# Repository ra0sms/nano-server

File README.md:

# Nano Server — Remote Radio Station Server

**Nano Server** is a server-side component of a remote ham radio station system. It runs on a **NanoPi NEO** single-board computer with **Armbian** and provides audio streaming, PTT control via GPIO, video streaming, relay switching, CAT interface forwarding, CW keying, and a web-based configuration interface.

Desktop client software: https://github.com/ra0sms/caesar-client-desktop

---

## Features

- 🎙️ **Bidirectional audio** over UDP (GStreamer + Opus codec)
- 📡 **PTT control** via GPIO with client reachability monitoring
- 📷 **Video streaming** via mjpg-streamer (MJPEG over HTTP)
- 🔌 **Relay control** via I2C (2×PCF8574T, 16 relays total)
- 🌐 **Web interface** — relays, TRX, band relay rules, audio, config, settings, self-update (single UI on port 5050)
- 🔗 **CAT interface** forwarding over TCP (Icom CI-V, Kenwood and Elecraft protocols; Elecraft is the Kenwood protocol with RTS/DTR held low, as the K3 needs)
- 🔄 **UART1 transparent relay** — CAT data duplicated to physical UART1 port for local computer access
- 🔒 **Fail-safe** — PTT is forced OFF when client disconnects; a CW message in progress is stopped and the CW key line released too (with break-in the radio would otherwise keep transmitting on the key alone)
- 🚫 **PTT Lock** — relay switching (manual and band relay) is blocked while PTT is active to prevent accidental antenna switching during transmission
- 🎛️ **Band Relay Rules** — automatic relay switching based on transceiver frequency
- 🔑 **CW Keyer** — Winkeyer protocol over UDP, generates Morse code on GPIO PC1
- 🔄 **Self-update** — checks GitHub for a newer release tag, shows its changelog, and applies it (`git pull` + restart of all related systemd services) from the web UI

---

## Hardware

| Component | Details |
|---|---|
| SBC | NanoPi NEO (Allwinner H3) |
| OS | Armbian (Debian Bookworm or later) |
| Audio | USB sound card (C-Media USB Audio Device) |
| Camera | USB webcam on `/dev/video1` |
| Relay board | 2× I2C GPIO expander at `0x20` / `0x21` |
| CAT interface | USB-to-Serial (port chosen in web Settings tab, e.g. `/dev/ttyUSB0`) |
| CAT UART1 relay | Physical UART1 on `/dev/ttyS1` (pins 8-TX, 10-RX) |
| CON LED | GPIO PC2 (line 66) |
| PTT output | GPIO PC3 (line 67) |
| CW Keyer output | GPIO PC1 (line 65) |

---

## Architecture

```
Client PC                          NanoPi NEO (Server)
─────────────────────────────────────────────────────────
                    UDP :5000  ←──  Audio TX (mic → client)
                    UDP :5000  ──→  Audio RX (client → speaker)
                    UDP :5001  ──→  PTT commands (0/1)
                    UDP :5002  ←→   Ping / RTT monitoring
                    UDP :5003  ──→  CW Keyer (Winkeyer protocol, UDP)
                    TCP :5050  ←──  Web UI (Flask): relays, TRX, band relay, audio, config, settings, update (live status over SSE)
                    TCP :6789  ←──  CW XML-RPC (PyWinKeyerSerial / not1mm)
                    TCP :3001  ←──  CAT (Icom CI-V or Kenwood)

Local PC (UART1)                   NanoPi NEO (Server)
─────────────────────────────────────────────────────────
                    UART1 (ttyS1) ←→  Transparent CAT relay (bidirectional)
```

### Systemd services

| Service | Description |
|---|---|
| `ptt_server` | PTT + CW Keyer + client monitor + ping responder (single service, all GPIO) |
| `audio_server` | GStreamer audio TX (server mic → client) |
| `audio_client_on_server` | GStreamer audio RX (client → server speaker) |
| `relay-web` | Web UI: relays, TRX, band relay, audio, config, settings, update (port 5050) |
| `mjpeg-streamer` | MJPEG video stream from USB camera (localhost:8081 only; viewed through the web panel login) |
| `alsa_restore` | Restores ALSA mixer state at boot |

---

## Installation

### 1. Flash Armbian to SD card and boot NanoPi NEO

### 2. Clone the repository

```bash
git clone https://github.com/ra0sms/nano-server.git
cd /home/pi/nano-server
```

### 3. Run the install script as root

```bash
sudo bash install_server.sh
```

The script will:
- Install all required packages (GStreamer, Flask, gpiod, mjpg-streamer, etc.)
- Build and install **mjpg-streamer** from source
- Create `client_ip.cfg`, `server_ip.cfg`, and `web/password.txt` with defaults
- Configure hardware overlays in `/boot/armbianEnv.txt`
- Register and start all systemd services
- Add sudoers entries for `restart_services_on_server.sh`, `systemctl restart/stop/start relay-web`, and `alsactl store` (so Audio tab volume changes persist across reboot)

### 4. Set IP addresses

```bash
echo '192.168.1.100' > /home/pi/nano-server/client_ip.cfg   # IP of the client PC
echo '192.168.1.10'  > /home/pi/nano-server/server_ip.cfg   # IP of this server
```

Or use the web interface at `http://<server-ip>:5050/`.

### 5. Change the default password for the web panel

```bash
echo 'yourpassword' > /home/pi/nano-server/web/password.txt
```

### 6. (Optional) Fix ALSA card order

If you have multiple USB audio devices (e.g., webcam with mic), the C-Media USB Audio card may not be card 0. Run:

```bash
sudo bash /home/pi/nano-server/fix_alsa_card_order.sh
sudo reboot
```

### 7. Reboot

```bash
sudo reboot
```

---

## Armbian Hardware Configuration

The script `setup_armbian_env.sh` patches `/boot/armbianEnv.txt` to enable the required device tree overlays. It **never modifies** `rootdev` or `rootfstype` so the system remains bootable.

To apply manually on a running system:

```bash
sudo bash /home/pi/nano-server/setup_armbian_env.sh
sudo reboot
```

Required overlays: `i2c0 uart1 uart2 uart3 usbhost0 usbhost1 usbhost2 usbhost3 w1-gpio`

---

## Web Interface — port 5050

Access at `http://<ip>:5050/` (password protected).
Default password: `1234` — change it in `web/password.txt`.

| Tab | Description |
|---|---|
| Main | Relay switching (16 relays, toggle/switch modes) and camera view |
| TRX | Transceiver frequency, band, mode display, and **Band Relay** frequency-based automatic relay switching rules |
| Audio | Speaker and mic level control via ALSA, audio stream settings (sample rate/buffer), restart audio services |
| Config | IP addresses, saved profiles, network status (client RTT / connection status, local IP) |
| Settings | Relay names, group modes, TRX serial port and protocol, UART1 transparent relay toggle |
| Update | Check GitHub for a newer release, view its changelog, apply the update and restart the web panel |

### Persistent Status Bar & Real-Time Updates

A **status bar** is shown at the top of every tab with the current PTT state, the transceiver online/frequency indicator, and the client link latency (RTT):

- **PTT** — turns red (`● PTT: ON`) while transmitting, grey otherwise.
- **TRX** — `🟢 ONLINE` / `🔴 OFFLINE` plus the live frequency.
- **Client** — round-trip time to the client PC in milliseconds.

Live values are pushed to the browser over **Server-Sent Events** (SSE, `GET /events`). The server sends a combined snapshot (PTT, relay state, TRX frequency/band/mode, client RTT, band-relay current state) that is emitted only when it changes, replacing the previous per-tab HTTP polling every 2 s. This makes status changes appear immediately and reduces load on the device. The SSE stream requires an authenticated session (cookies are sent automatically by the browser) and reconnects automatically if dropped.

### Band Relay Rules

Configure which relays activate for each frequency range (in kHz). Rules use `from ≤ freq < to` logic (lower bound inclusive, upper bound exclusive). To avoid gaps, set `to` of one rule equal to `from` of the next.

Example:
- `1800-1840` kHz → relays 1, 2
- `1840-1900` kHz → relays 3, 4
- `7000-7300` kHz → relays 5, 6

Auto-switching can be toggled on/off via a checkbox in the TRX tab. Rules are validated on the server (numeric `from < to` in kHz, relay numbers 1–16); if `web/band_rules.json` is unreadable at startup, it is renamed to `band_rules.json.invalid` and the default rules are used.

**Group-scoped auto-switching:** auto-switching only touches the relay group(s) that the configured rules actually reference, leaving the other group fully manual:

- If the saved rules only use relays **1–8**, then relays **9–16** are never reset or switched automatically — they can be selected manually and their state is preserved across every frequency change (and vice versa).
- If the rules reference relays from both groups, both are auto-managed (all selected relays are reset and re-applied as before).
- If no rule references any relay, auto-switching leaves all 16 relays untouched.

This makes it possible to dedicate one relay group to automatic antenna/band switching while keeping the other group for manually-controlled devices.

**Switching only on a band change, with confirmation:** relays are switched only when the frequency moves into a range with a *different* relay set, and only after two frequency readings at least 0.3 s apart agree. This means:

- a single corrupted CAT frame can't flip the antenna;
- tuning back and forth across a range boundary doesn't chatter the relays;
- a relay toggled by hand inside an auto-managed group stays as set until the next band change (it is no longer reset on every CAT reading).

While a band change waits for its confirming reading, the server polls the transceiver right away (subject to the external-program collision guard), so the switch still happens promptly. Saving the rules or re-enabling auto-switching re-applies them on the next reading.

### PTT Lock — Relay Protection During Transmission

When PTT is active (transmitting), all relay switching is automatically blocked to prevent accidental antenna switching during transmission. This protects both the transceiver and the antenna system.

**How it works:**
1. [`combined_ptt_service.py`](network/combined_ptt_service.py) broadcasts the GPIO PTT status via UDP on `127.0.0.1:5004` on every change **and as a heartbeat every ~0.3 s**
2. [`web/app.py`](web/app.py) listens for these broadcasts in a background thread. If no status has arrived for 1.5 s (the web panel just restarted, or `ptt_server` is stopped/crashed), the PTT state is treated as **unknown and relays stay locked**
3. **CAT PTT** is tracked too, since programs like JTDX/WSJT-X/flrig often key the radio over CAT instead of the GPIO line:
   - TX/RX commands external programs send through the TCP port or UART1 relay (Kenwood `TX…;` / `RX…;`, Icom CI-V `1C 00 01` / `1C 00 00`)
   - the radio's own reports: TX/RX flag in the Kenwood `IF` reply and `TX…;`/`RX…;` auto-information, the Icom reply to `1C 00` (the server polls it on alternate poll cycles)
   - if the transceiver stops answering CAT for 5 s, the CAT TX state is cleared
4. Both manual relay toggle and automatic band relay switching are blocked while GPIO PTT is on, CAT PTT is on, or the PTT state is unknown
5. The web interface visually disables relay buttons (dimmed, `not-allowed` cursor). The status bar shows `PTT: ON`, `PTT: ON (CAT)`, or an orange `PTT: NO STATUS` when `ptt_server` isn't reporting

**Blocked operations:**
- Manual relay toggle via web UI buttons
- Automatic band relay switching when transceiver frequency changes
- Direct API calls to `POST /toggle/<n>` (server-side check)
- **Retuning from the web UI** — frequency step, band buttons and `/trx/set_freq`: band relays can't follow during TX, so a band change would leave the transmitter keyed into the previous band's antenna (the request is refused with HTTP 409 and a message in the UI). Frequency steps are also refused while the transceiver is offline, instead of stepping from a made-up frequency

---

### UART1 Transparent CAT Relay

The server can transparently relay all CAT data between the transceiver (connected via the USB-to-Serial CAT port selected in web Settings) and a local computer connected to the **UART1** physical port (`/dev/ttyS1`, pins 8-TX, 10-RX on NanoPi NEO). This allows two clients to share the same CAT connection simultaneously:

- **Remote client** — connects via TCP port 3001 over the network. Only `127.0.0.1`, the client IP from `client_ip.cfg`, and the IPs listed in `tcp_allowed_ips` in `web/trx_config.json` (edit the file, then restart `relay-web`; e.g. `"tcp_allowed_ips": ["192.168.1.50"]`) may connect; other connections are closed immediately, since this port can key and retune the transmitter
- **Local computer** — connected directly via UART1 (e.g., a PC next to the server)

**How it works:**

1. All data received from the transceiver on the CAT port is duplicated to both TCP clients and UART1
2. All data received from UART1 is written back to the CAT port (and thus forwarded to the transceiver)
3. All data received from TCP clients is written to the CAT port (existing behavior)

**Configuration** (in [`web/trx_config.json`](web/trx_config.json) or via web UI Settings tab):

```json
{
    "uart1_enabled": true,
    "uart1_port": "/dev/ttyS1"
}
```

The UART1 baudrate is automatically set to match the CAT port baudrate.

**Replies to the server's own requests are not forwarded.** The server's own polls (and the web UI's TRX commands) would otherwise produce replies that external programs take as answers to their own requests, causing "unexpected reply" errors and retries in Hamlib/JTDX/flrig:

- **Icom CI-V:** the server talks to the radio from its own controller address, **Server CI-V Address** in Settings (`server_addr`, default `0xE1`), not the `0xE0` that flrig/JTDX/Hamlib use (`ctrl_addr`). The radio replies to the sender's address, so frames to or from `server_addr` (including the echo on a single-wire CI-V bus) are decoded for the web UI but not passed to TCP clients or UART1. If some radio only works with `0xE0`, set Server CI-V Address to `0xE0`: everything is then forwarded, as in older versions.
- **Kenwood:** there are no addresses, so after each `IF;` poll the next `IF…;` reply (within 0.5 s) is kept back from external programs. If UART1 is unavailable (e.g., overlay not enabled), the server logs a warning and continues without it.

**Web UI toggle:** The **Settings → Transceiver Settings** tab now includes a **"UART1 transparent relay"** checkbox. It can be turned on/off directly from the web interface and takes effect immediately (the relay is re-initialized without restarting the service).

**Poller behavior with the relay enabled:**

When the UART1 transparent relay is enabled, the CAT bus can be owned by an external program on the PC (e.g. **flrig**, **TR4W**, **Hamlib**). While the external program is **actively** exchanging data, the server's internal poller backs off so its queries do not interleave with the PC's requests on the same line and corrupt the response stream.

However, the server now **automatically resumes its own polling whenever the external program is silent or absent**:

- **Relay ON + external program active** → the server's poller stays quiet; the PC program reads the transceiver directly, and the web **TRX tab** stays updated passively by decoding the responses that flow through the bridge.
- **Relay ON + external program silent/absent** → the server only skips its own poll while an external controller (via UART1 or a TCP client) has sent something within the last 0.3 s, or while the radio has answered within the last 2 s (someone is already keeping the frequency fresh). Otherwise it polls the transceiver itself, so the web **TRX tab** still shows the live frequency/mode even when no PC program is running. As soon as the external program sends traffic again, the poller hands the port back within one poll cycle.
- **Relay OFF** → internal poller enabled; the web interface queries the transceiver itself and updates the TRX tab even when no PC program is connected.

This behavior applies to **both** CAT protocols (Icom CI-V and Kenwood).

"Recently" means the radio has reported the **active** frequency in the last 2 s; other CAT traffic doesn't count (e.g. Hamlib reading only the inactive VFO).

**What the web panel decodes:**

- **Icom CI-V:** frequency and mode replies (`03`/`04`) and the radio's own **transceive** reports (`00`/`01`). With *CI-V Transceive* enabled in the radio's menu, frequency changes arrive as soon as the dial moves, so band relays react without waiting for a poll. Modes: LSB, USB, AM, CW, CW-R, RTTY, RTTY-R, FM, WFM, DV, DD. 6-byte frequencies (10 GHz+ bands, IC-905) are supported.
- **Kenwood:** `IF` (frequency, mode, TX/RX and **active VFO**), `FA`/`FB`, `MD`, `FR`. `FA`/`FB` only update the displayed frequency and band relays when they are for the VFO the radio is operating on (learned from `IF`, `FR` reports and `FR` commands external programs send). Otherwise, working on VFO B would switch antennas by VFO A's frequency. Frequency changes from the web UI are sent to the active VFO (`FB` when on VFO B).

**Stability & auto-recovery:**

All writes to the CAT port are serialized through a single thread lock (`ser_lock`), and data from each external source (every TCP client and UART1) is first split into **whole CAT frames** (terminated by `;` for Kenwood, `0xFD` for CI-V) — only complete frames are written. So a command that arrives in pieces (e.g. `F` in one TCP segment and `A;` in the next) can never have the poller's or another client's frame inserted into its middle. An unterminated tail is passed through as-is after 0.5 s. The CAT port and UART1 are read without a fixed 100 ms wait, so replies reach JTDX/flrig and UART1 immediately. Additionally, if the CAT serial port raises a read error (e.g. a temporary USB hiccup or the transceiver is powered off), the server now **automatically closes and reopens the serial ports** with retries instead of silently stalling — so a remote `JTDX`, `flrig`, or `WSJT-X` session no longer needs a full service restart to recover. Manually re-initializing from the web UI (Reconnect button / `POST /trx/reinit`) and re-initializing after a config change are also guarded by the same lock.

**Prerequisite:** UART1 overlay must be enabled in `/boot/armbianEnv.txt`:
```
overlays=i2c0 uart1 uart2 uart3 usbhost0 usbhost1 usbhost2 usbhost3 w1-gpio
```

---

## Profiles

Up to 5 configuration profiles (server IP, client IP, audio settings) can be saved and loaded from the web configuration interface. Profile files are stored in `profiles/`.

---

## Restarting Services

To restart all runtime services at once:

```bash
sudo /home/pi/nano-server/restart_services_on_server.sh
```

Or restart individual services:

```bash
sudo systemctl restart ptt_server.service
sudo systemctl restart audio_server.service
```

To restart the web panel from the UI, use the **"Restart Web Panel"** button on the Update tab (requires sudoers NOPASSWD for `systemctl restart relay-web`). The **"Restart Audio Services"** button on the Audio tab restarts `audio_server`, `audio_client_on_server`, `mjpeg-streamer`, and `ptt_server` (via `restart_services_on_server.sh`).

To reload `client_ip.cfg` without restarting the PTT service:

```bash
sudo systemctl kill -s SIGHUP ptt_server.service
```

---

## Software Update

The **Update** tab checks GitHub for a newer release and applies it without needing SSH access to the server.

- **Check for Update** fetches tags from `origin` and compares the highest `vX.Y.Z` tag to the version reachable from the currently checked-out commit (`git describe --tags`). If a newer one exists, it shows every `CHANGELOG.txt` section newer than the current version (not just the latest one), read directly from the fetched tag so it's visible even before pulling.
- **Update** runs `git pull --ff-only`, then restarts `audio_server`, `audio_client_on_server`, `mjpeg-streamer`, and `ptt_server` (via `restart_services_on_server.sh`), and finally restarts `relay-web` itself.
- Before pulling, it refuses if the checkout has local changes to any **tracked** file, or **any untracked file at all**, outside of the app's own runtime-state files (`web/config.json`, `audio/audio_config.cfg`, `web/trx_config.json`, `web/band_rules.json` — these are gitignored and rewritten by the app itself, so their local content is preserved across the pull automatically). A stray file left in the checkout (e.g. a manual backup) will block the update until it's removed or committed elsewhere.

Cutting a new release: add a `## vX.Y.Z (date)` section with a bullet list to the top of `CHANGELOG.txt`, commit, then tag and push:

```bash
git tag vX.Y.Z
git push origin main
git push origin vX.Y.Z
```

---

## Audio Configuration

Edit `audio/audio_config.cfg`:

```ini
RATE=48000       # sample rate: 48000 or 24000 Hz
LATENCY=100000   # buffer time in microseconds (100 ms)
```

Or use the **Audio Stream Settings** section on the **Audio** page in the web UI.

The web panel auto-detects the ALSA card (looks for C-Media USB Audio in `/proc/asound/cards`) and the speaker control name. Mic capture is hardcoded to `numid=8` (`Mic Capture Volume`).

---

## CW Keyer (Winkeyer Protocol)

The CW Keyer is integrated into the **`ptt_server`** service (single process, single GPIO request). It implements the **K1EL Winkeyer protocol** over UDP, generating Morse code (CW) on **GPIO PC1** (line 65).

All GPIO lines (CW=PC1, CON=PC2, PTT=PC3) are requested in a single `gpiod.request_lines()` call to avoid conflicts between separate processes on the same gpiochip.

### How it works

1. The client sends Winkeyer protocol commands via UDP to port **5003**
2. The server buffers ASCII characters and sends them as CW on GPIO PC1
3. The output pin (PC1) drives a transistor/keying circuit connected to the transceiver

### Supported commands

| Byte | Command | Description |
|---|---|---|
| `0x00` + WPM | Set speed | WPM value (5-99) |
| `0x02` | Start sending | Begin transmitting buffer |
| `0x03` | Clear buffer | Reset and stop |
| `0x0A` (LF) | Start sending | Same as 0x02 |
| `0x1B` | Immediate stop | Abort transmission |
| `0x1F` | Request status | Reply: 0x00 (idle) or 0x01 (busy) |
| `0x20`-`0x7E` | ASCII chars | Add to send buffer |
| `0x7F` | Backspace | Remove last char from buffer |

### Usage

```bash
# Send "CQ CQ DE RA0SMS" at 25 WPM
echo -ne '\x00\x19CQ CQ DE RA0SMS\x0a' | nc -u <server-ip> 5003
```

### XML-RPC interface (PyWinKeyerSerial / not1mm compatible)

The service provides an **XML-RPC server on TCP port 6789**, compatible with the [K6GTE PyWinKeyerSerial](https://github.com/mbridak/PyWinKeyerSerial) interface. This allows logging programs like **[not1mm](https://github.com/mbridak/not1mm)** to send CW directly to the server.

**Port 6789 is the CW connection used by not1mm.** In not1mm's CW settings this corresponds to `cwport = 6789` with `cwtype = 2` (`PyWinKeyerSerial`). The corresponding not1mm UI fields are:
- **Settings → CW Interface → Type**: `PyWinKeyerSerial`
- **Settings → CW Interface → IP**: `<server-ip>`
- **Settings → CW Interface → Port**: `6789`

> ⚠️ **Important — re-check not1mm.json manually after any IP change.** not1mm stores its CW server address in the **`cwip`** field of its settings file **`~/.config/not1mm/not1mm.json`**. If the IP address of this Nano Server changes, you must edit `cwip` in that file (and ideally restart not1mm), because **not1mm will not start / will fail to work if the configured `cwip` is unreachable**. The `cwport` (must be `6789`) and `cwtype` (must be `2`) are stored there as well.

Example `~/.config/not1mm/not1mm.json` (relevant CW fields):

```json
{
    "cwip": "10.0.1.16",
    "cwport": 6789,
    "cwtype": 2,
    "useflrig": true,
    "cw_speed": 30
}
```

Available RPC methods:

| Method | Description |
|---|---|
| `k1elsendstring(text)` | Send a string to the CW buffer and start transmitting |
| `setspeed(wpm)` | Set CW speed (5-99 WPM) |
| `sendblended(text)` | Send a prosign/blended message |
| `tuneon()` | Key down and hold (tune mode) |
| `tuneoff()` | Stop key down |
| `clearbuffer()` | Clear the CW buffer and stop sending |

Example using Python:

```python
import xmlrpc.client
proxy = xmlrpc.client.ServerProxy("http://<server-ip>:6789/RPC2")
proxy.k1elsendstring("CQ CQ DE RA0SMS")
proxy.setspeed(25)
```

### Service management

```bash
sudo systemctl status ptt_server.service
sudo systemctl restart ptt_server.service
sudo journalctl -u ptt_server.service -f
```

---

## Project Structure

```
nano-server/
├── install_server.sh              # Main installation script
├── setup_armbian_env.sh           # Patches /boot/armbianEnv.txt safely
├── restart_services_on_server.sh  # Restart all runtime services
├── fix_alsa_card_order.sh         # Fix USB audio card order via modprobe
├── setup_sudo_nopasswd.sh         # Configure sudoers for web panel self-restart
├── create_ser2net_yaml.sh         # Generate ser2net config
├── client_ip.cfg                  # Client IP (git-ignored)
├── server_ip.cfg                  # Server IP (git-ignored)
├── CHANGELOG.txt                  # Per-version release notes, read by the Update tab
├── armbianEnv.txt                 # Reference overlay config
├── audio/
│   ├── audio_server.sh            # GStreamer TX pipeline
│   ├── audio_client_on_server.sh  # GStreamer RX pipeline
│   └── audio_config.cfg           # Rate and buffer settings (git-ignored, written by the app)
├── network/
│   └── combined_ptt_service.py    # PTT + CW Keyer + client monitor + ping responder
├── web/
│   ├── app.py                     # Web UI: relays, TRX, band relay, audio, config, settings, update (+ live status via SSE /events)
│   ├── templates/index.html       # Web UI page markup (rendered via render_template)
│   ├── static/css/style.css       # Web UI stylesheet
│   ├── static/js/main.js          # Web UI client-side logic
│   ├── config.json                # Relay names and group modes (git-ignored, written by the app)
│   ├── trx_config.json            # TRX serial port and protocol settings (git-ignored, written by the app)
│   ├── band_rules.json            # Band relay frequency rules (git-ignored, written by the app)
│   └── password.txt               # Web UI password (git-ignored)
├── systemd/                       # Service unit files
├── profiles/                      # Saved configuration profiles (git-ignored)
└── docs/
    ├── gpio-info.txt              # GPIO line numbers reference
    └── nano-pinout.jpg            # NanoPi NEO pinout diagram
└── KiCad/                         # KiCad schematic and PCB files   
```

---

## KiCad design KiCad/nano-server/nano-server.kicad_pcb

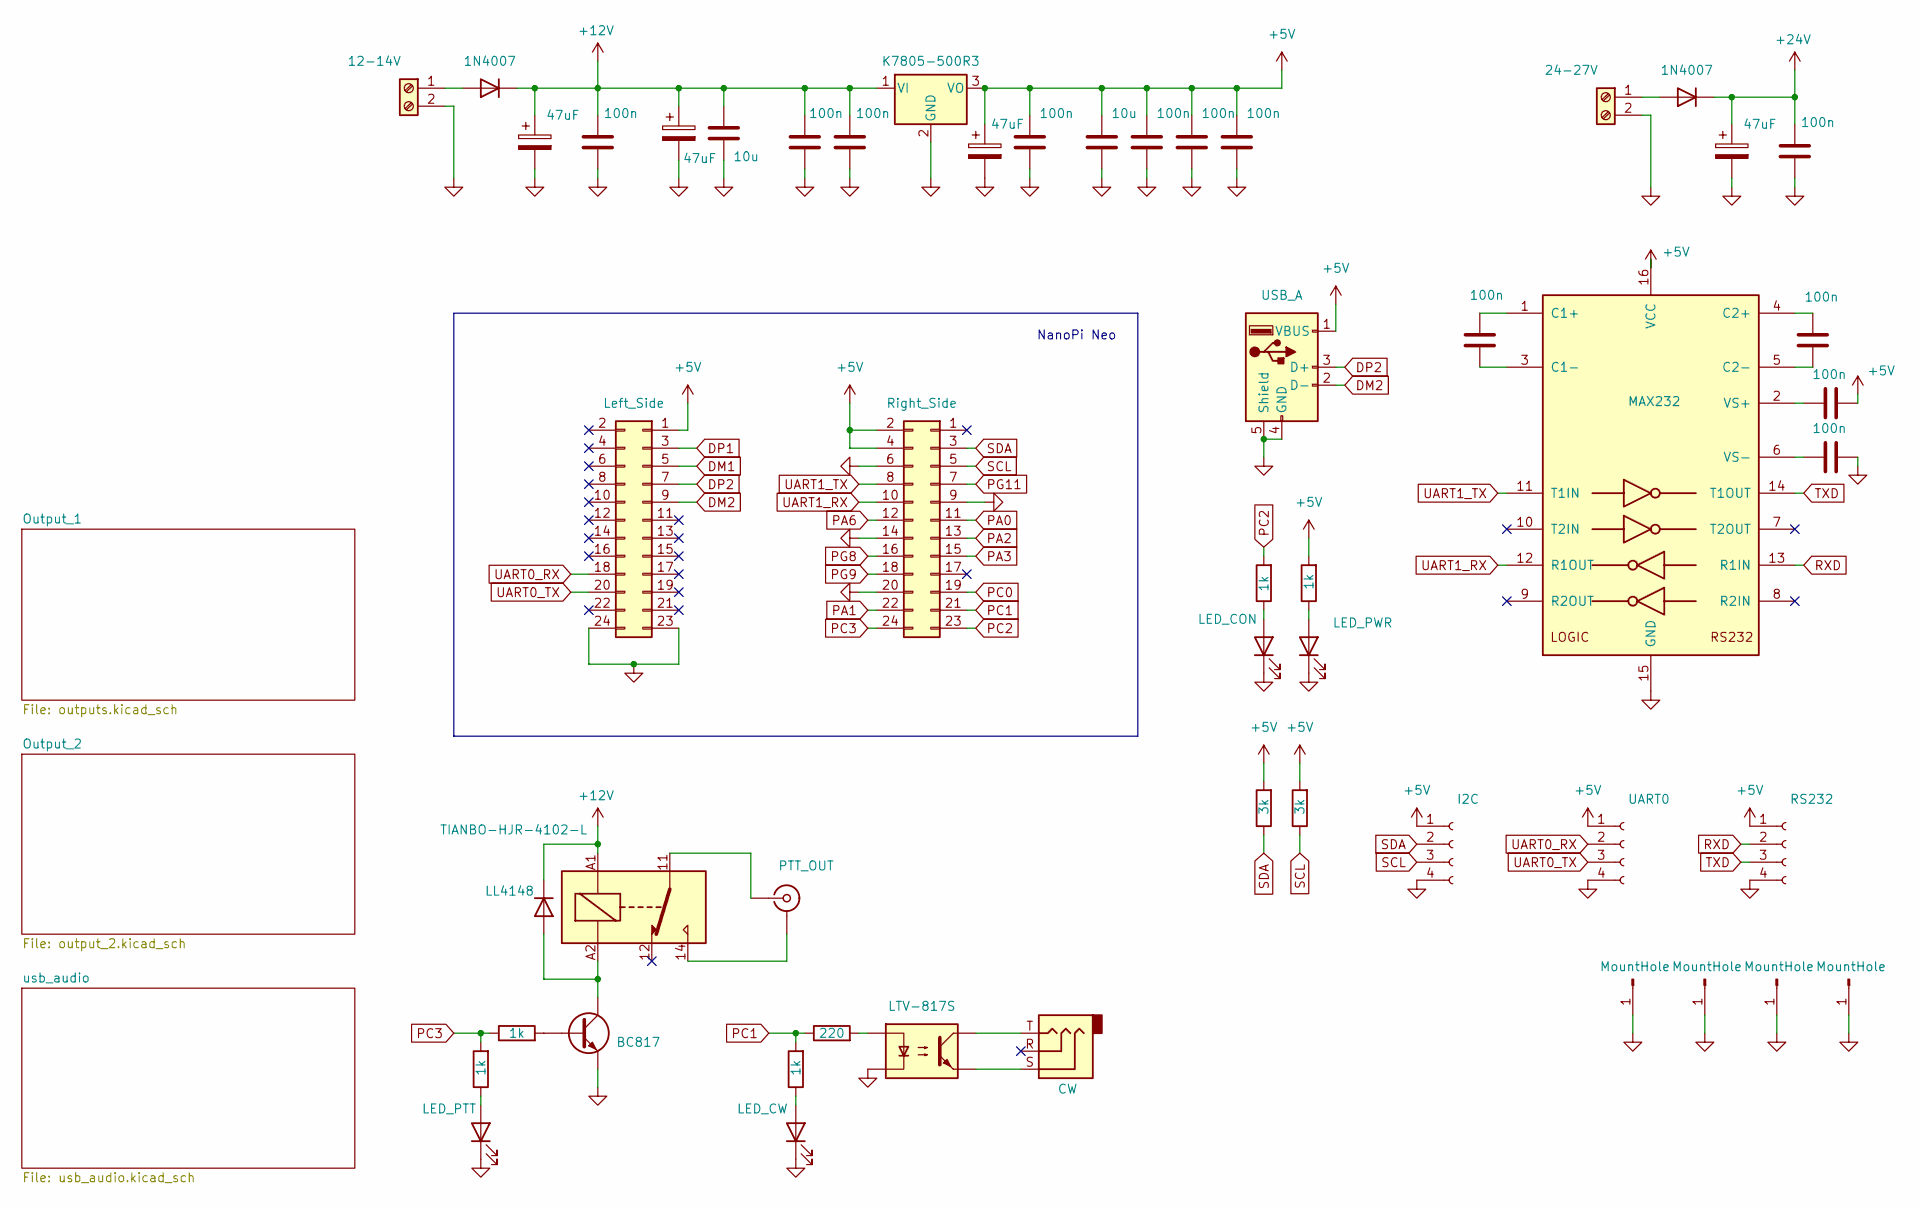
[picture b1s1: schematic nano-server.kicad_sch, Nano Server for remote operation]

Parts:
C1, C3, C7, C29: 47uF; CP_Radial_D5.0mm_P2.50mm
C2, C5, C6, C8, C10, C11, C12, C15, C16, C17, C30, C33: 100n; C_1206_3216Metric
C4, C9: 10u; C_1206_3216Metric_Pad1.33x1.80mm_HandSolder
D1, D8: 1N4007; D_DO-41_SOD81_P10.16mm_Horizontal
D2: LED_CON; PinHeader_1x02_P2.54mm_Vertical
D3: LED_PWR; PinHeader_1x02_P2.54mm_Vertical
D4: LED_PTT; PinHeader_1x02_P2.54mm_Vertical
D5: LL4148; D_MiniMELF
D25: LED_CW; LED_1206_3216Metric
J1: 12-14V; TerminalBlock_MaiXu_MX126-5.0-02P_1x02_P5.00mm
J2: Left_Side; PinSocket_2x12_P2.54mm_Vertical
J3: Right_Side; PinSocket_2x12_P2.54mm_Vertical
J4: USB_A; USB_A_Wuerth_614004134726_Horizontal
J5: PTT_OUT; PinHeader_1x02_P2.54mm_Vertical
J10: 24-27V; TerminalBlock_MaiXu_MX126-5.0-02P_1x02_P5.00mm
J13, J14, J15, J16: MountHole; MountingHole_3.2mm_M3_DIN965_Pad
J17: I2C; PinHeader_1x04_P2.54mm_Vertical
J18: CW; Jack_3.5mm_CUI_SJ-3523-SMT_Horizontal
J19: UART0; PinHeader_1x04_P2.54mm_Vertical
J20: RS232; PinHeader_1x04_P2.54mm_Vertical
K1: TIANBO-HJR-4102-L; Relay_SPDT_CUI_SR5
Q1: BC817; SOT-23
R1, R2, R3, R4, R32: 1k; R_1206_3216Metric
R14, R15: 3k; R_1206_3216Metric
R33: 220; C_1206_3216Metric
U1: K7805-500R3; TO-220-3_Vertical
U15: LTV-817S; SMDIP-4_W9.53mm
U16: MAX232; SOIC-16_3.9x9.9mm_P1.27mm

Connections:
+5V: C7.1, C8.1, C9.1, C10.1, C11.1, C12.1, C17.2, J2.1, J3.2, J3.4, J4.1 (VBUS), J17.1, J19.1, J20.1, R2.2, R14.2, R15.2, U1.3 (VO), U16.16 (VCC); also elsewhere on the board
+12V: C1.1, C2.1, C3.1, C4.1, C5.1, C6.1, D1.1 (K), D5.1 (K), K1.A1, U1.1 (VI); also elsewhere on the board
+24V: C29.1, C30.1, D8.1 (K); also elsewhere on the board
DM1: J2.5; also elsewhere on the board
DM2: J2.9, J4.2 (D-)
DP1: J2.3; also elsewhere on the board
DP2: J2.7, J4.3 (D+)
GND: C1.2, C2.2, C3.2, C4.2, C5.2, C6.2, C7.2, C8.2, C9.2, C10.2, C11.2, C12.2, C29.2, C30.2, C33.2, D2.1 (K), D3.1 (K), D4.1 (K), D25.1 (K), J1.2, J2.23, J2.24, J3.6, J3.9, J3.14, J3.20, J4.4 (GND), J4.5 (Shield), J10.2, J13.1 (Pin_1_1), J14.1 (Pin_1_1), J15.1 (Pin_1_1), J16.1 (Pin_1_1), J17.4, J19.4, J20.4, Q1.2 (E), U1.2 (GND), U15.2, U16.15 (GND); also elsewhere on the board
unnamed: D1.2 (A), J1.1
unnamed: D2.2 (A), R1.1
unnamed: D3.2 (A), R2.1
unnamed: D4.2 (A), R3.1
unnamed: D5.2 (A), K1.A2, Q1.3 (C)
unnamed: D8.2 (A), J10.1
unnamed: D25.2 (A), R32.1
unnamed: J5.2 (Ext), K1.14
unnamed: J5.1 (In), K1.11
unnamed: J18.S, U15.3
unnamed: J18.T, U15.4
unnamed: Q1.1 (B), R4.2
unnamed: R33.2, U15.1
unnamed: C15.1, U16.1 (C1+)
unnamed: C15.2, U16.3 (C1-)
unnamed: C16.1, U16.4 (C2+)
unnamed: C16.2, U16.5 (C2-)
unnamed: C17.1, U16.2 (VS+)
unnamed: C33.1, U16.6 (VS-)
PA0: J3.11
PA1: J3.22
PA2: J3.13
PA3: J3.15
PA6: J3.12
PC0: J3.19
PC1: J3.21, R32.2, R33.1
PC2: J3.23, R1.2
PC3: J3.24, R3.2, R4.1
PG8: J3.16
PG9: J3.18
PG11: J3.7
RXD: J20.2, U16.13 (R1IN)
SCL: J3.5, J17.3, R15.1; also elsewhere on the board
SDA: J3.3, J17.2, R14.1; also elsewhere on the board
TXD: J20.3, U16.14 (T1OUT)
UART0_RX: J2.18, J19.2
UART0_TX: J2.20, J19.3
UART1_RX: J3.10, U16.12 (R1OUT)
UART1_TX: J3.8, U16.11 (T1IN)

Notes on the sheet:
NanoPi Neo

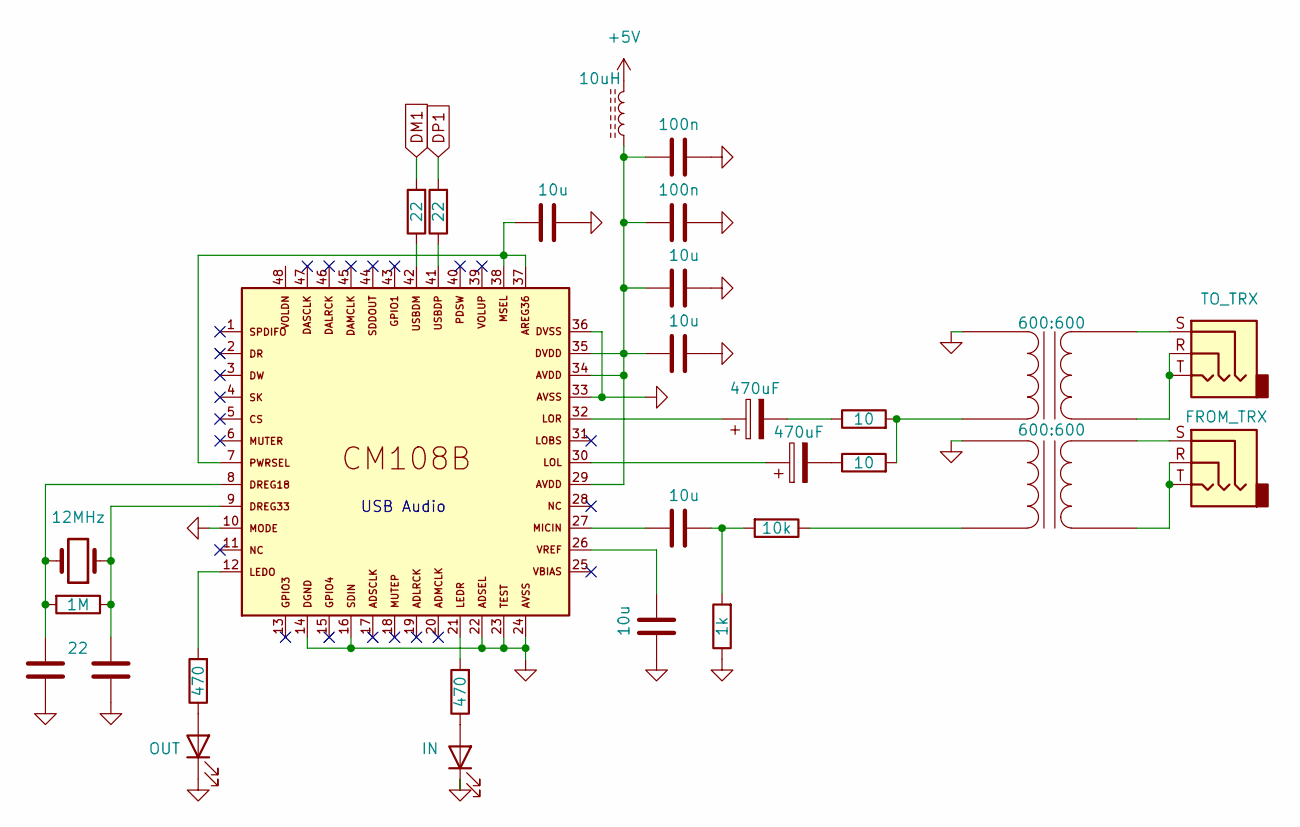
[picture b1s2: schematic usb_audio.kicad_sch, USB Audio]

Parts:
C18, C19: 22; C_1206_3216Metric_Pad1.33x1.80mm_HandSolder
C20, C21, C24, C25, C26: 10u; C_1206_3216Metric_Pad1.33x1.80mm_HandSolder
C22, C23: 100n; C_1206_3216Metric
C27, C28: 470uF; CP_Radial_D5.0mm_P2.50mm
D6: OUT; LED_1206_3216Metric
D7: IN; LED_1206_3216Metric
J8: TO_TRX; Jack_3.5mm_CUI_SJ-3523-SMT_Horizontal
J9: FROM_TRX; Jack_3.5mm_CUI_SJ-3523-SMT_Horizontal
L4: 10uH; R_1206_3216Metric
R5: 1M; R_1206_3216Metric
R6, R9: 470; R_1206_3216Metric
R7, R8: 22; R_1206_3216Metric
R10: 1k; R_1206_3216Metric
R11: 10k; R_1206_3216Metric
R12, R13: 10; R_1206_3216Metric
T1, T2: 600:600; Transformer_NF_ETAL_1-1_P1200
U8: CM108B; LQFP-48_7x7mm_P0.5mm
Y1: 12MHz; Crystal_HC18-U_Vertical

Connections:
+5V: L4.2; also elsewhere on the board
DM1: R7.2; also elsewhere on the board
DP1: R8.2; also elsewhere on the board
GND: C18.1, C19.1, C20.2, C21.1, C22.2, C23.2, C24.2, C25.2, D6.1 (K), D7.1 (K), R10.1, T1.1 (AA), T2.1 (AA), U8.10, U8.14, U8.16, U8.22, U8.23, U8.24, U8.33, U8.36; also elsewhere on the board
unnamed: C18.2, R5.2, U8.8, Y1.2
unnamed: C19.2, R5.1, U8.9, Y1.1
unnamed: C20.1, U8.7, U8.37, U8.38
unnamed: C21.2, U8.26
unnamed: C22.1, C23.1, C24.1, C25.1, L4.1, U8.29, U8.34, U8.35
unnamed: C26.1, U8.27
unnamed: C26.2, R10.2, R11.2
unnamed: C27.1, U8.32
unnamed: C27.2, R12.1
unnamed: C28.1, U8.30
unnamed: C28.2, R13.1
unnamed: D6.2 (A), R6.1
unnamed: D7.2 (A), R9.1
unnamed: R6.2, U8.12
unnamed: R7.1, U8.42
unnamed: R8.1, U8.41
unnamed: R9.2, U8.21
unnamed: R12.2, R13.2, T1.3 (AB)
unnamed: J8.R, J8.T, T1.4 (SA)
unnamed: J8.S, T1.6 (SB)
unnamed: R11.1, T2.3 (AB)
unnamed: J9.R, J9.T, T2.4 (SA)
unnamed: J9.S, T2.6 (SB)

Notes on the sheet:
USB Audio

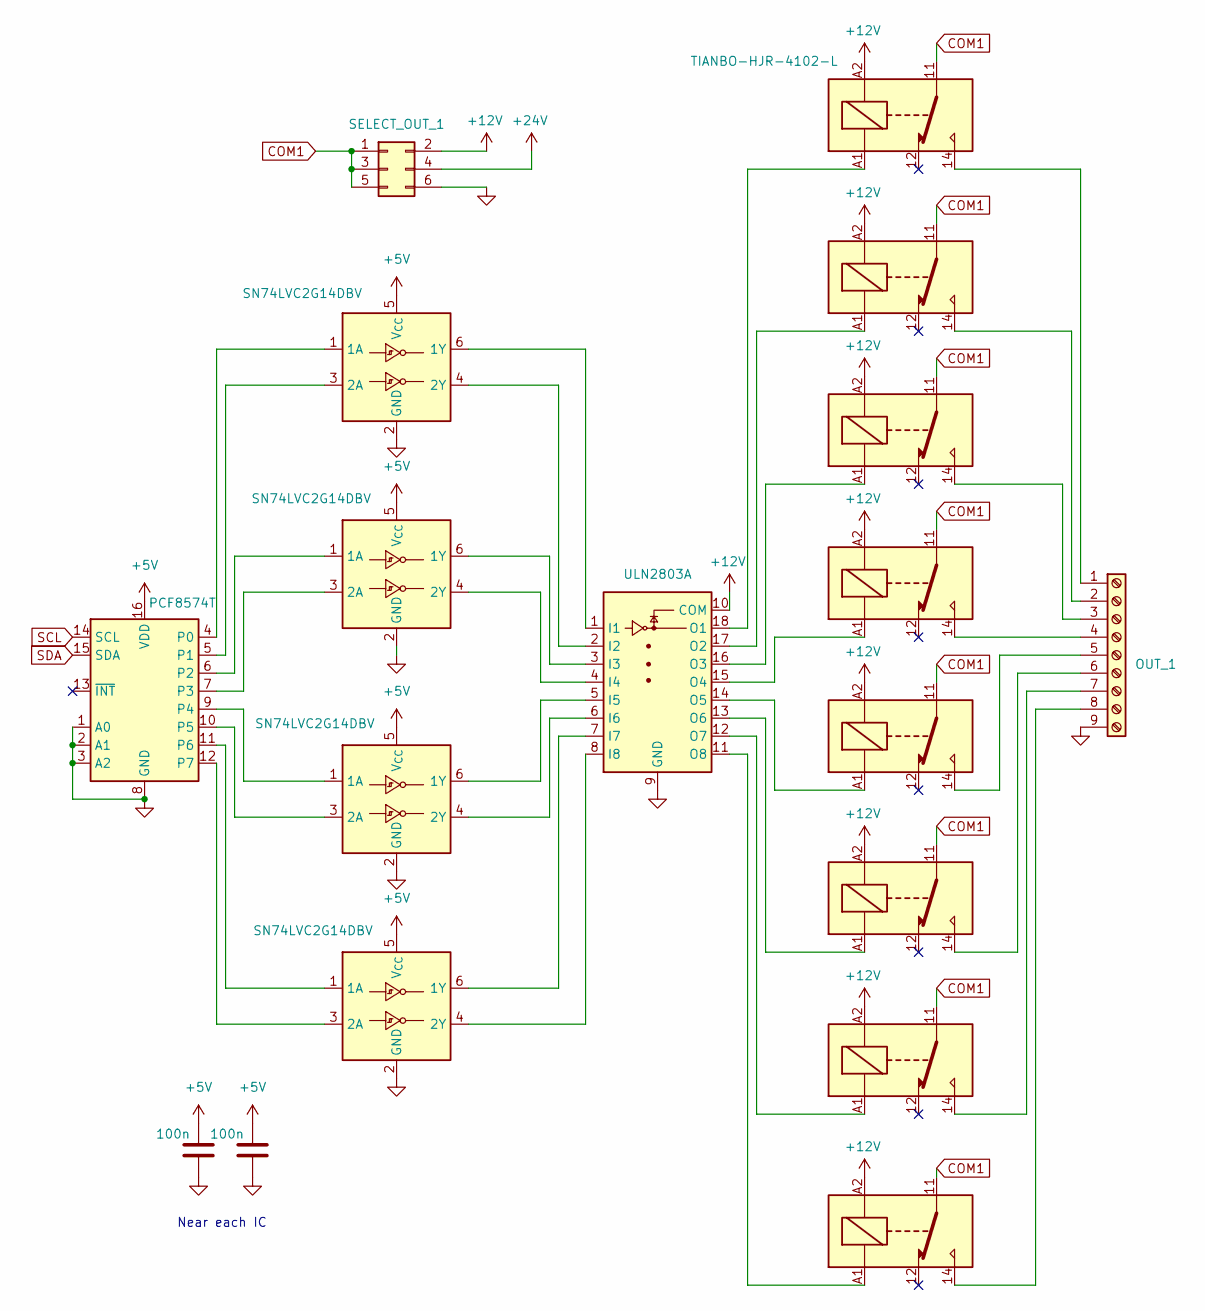
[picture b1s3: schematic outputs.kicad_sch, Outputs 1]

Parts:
C13, C14: 100n; C_1206_3216Metric
J7: OUT_1; TerminalBlock_MaiXu_MX126-5.0-09P_1x09_P5.00mm
J11: SELECT_OUT_1; PinHeader_2x03_P2.54mm_Vertical
K2, K18, K19, K20, K21, K22, K23, K24: TIANBO-HJR-4102-L; Relay_SPDT_CUI_SR5
U2: PCF8574T; SOIC-16W_7.5x10.3mm_P1.27mm
U3, U4, U5, U6: SN74LVC2G14DBV; SOT-23-6
U7: ULN2803A; SOIC-18W_7.5x11.6mm_P1.27mm

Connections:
+5V: C13.1, C14.1, U2.16 (VDD), U3.5 (V_{CC}), U4.5 (V_{CC}), U5.5 (V_{CC}), U6.5 (V_{CC}); also elsewhere on the board
+12V: J11.2, K2.A2, K18.A2, K19.A2, K20.A2, K21.A2, K22.A2, K23.A2, K24.A2, U7.10 (COM); also elsewhere on the board
+24V: J11.4; also elsewhere on the board
COM1: J11.1, J11.3, J11.5, K2.11, K18.11, K19.11, K20.11, K21.11, K22.11, K23.11, K24.11
GND: C13.2, C14.2, J7.9, J11.6, U2.1 (A0), U2.2 (A1), U2.3 (A2), U2.8 (GND), U3.2 (GND), U4.2 (GND), U5.2 (GND), U6.2 (GND), U7.9 (GND); also elsewhere on the board
unnamed: J7.1, K19.14
unnamed: J7.2, K2.14
unnamed: J7.3, K20.14
unnamed: J7.4, K18.14
unnamed: J7.5, K21.14
unnamed: J7.6, K24.14
unnamed: J7.7, K22.14
unnamed: J7.8, K23.14
unnamed: U2.4 (P0), U3.1 (1A)
unnamed: U2.5 (P1), U3.3 (2A)
unnamed: U2.6 (P2), U4.1 (1A)
unnamed: U2.7 (P3), U4.3 (2A)
unnamed: U2.9 (P4), U5.1 (1A)
unnamed: U2.10 (P5), U5.3 (2A)
unnamed: U2.11 (P6), U6.1 (1A)
unnamed: U2.12 (P7), U6.3 (2A)
unnamed: U3.6 (1Y), U7.1 (I1)
unnamed: U3.4 (2Y), U7.2 (I2)
unnamed: U4.6 (1Y), U7.3 (I3)
unnamed: U4.4 (2Y), U7.4 (I4)
unnamed: U5.6 (1Y), U7.5 (I5)
unnamed: U5.4 (2Y), U7.6 (I6)
unnamed: U6.6 (1Y), U7.7 (I7)
unnamed: U6.4 (2Y), U7.8 (I8)
unnamed: K19.A1, U7.18 (O1)
unnamed: K2.A1, U7.17 (O2)
unnamed: K20.A1, U7.16 (O3)
unnamed: K18.A1, U7.15 (O4)
unnamed: K21.A1, U7.14 (O5)
unnamed: K24.A1, U7.13 (O6)
unnamed: K22.A1, U7.12 (O7)
unnamed: K23.A1, U7.11 (O8)
SCL: U2.14 (SCL); also elsewhere on the board
SDA: U2.15 (SDA); also elsewhere on the board

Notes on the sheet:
Near each IC

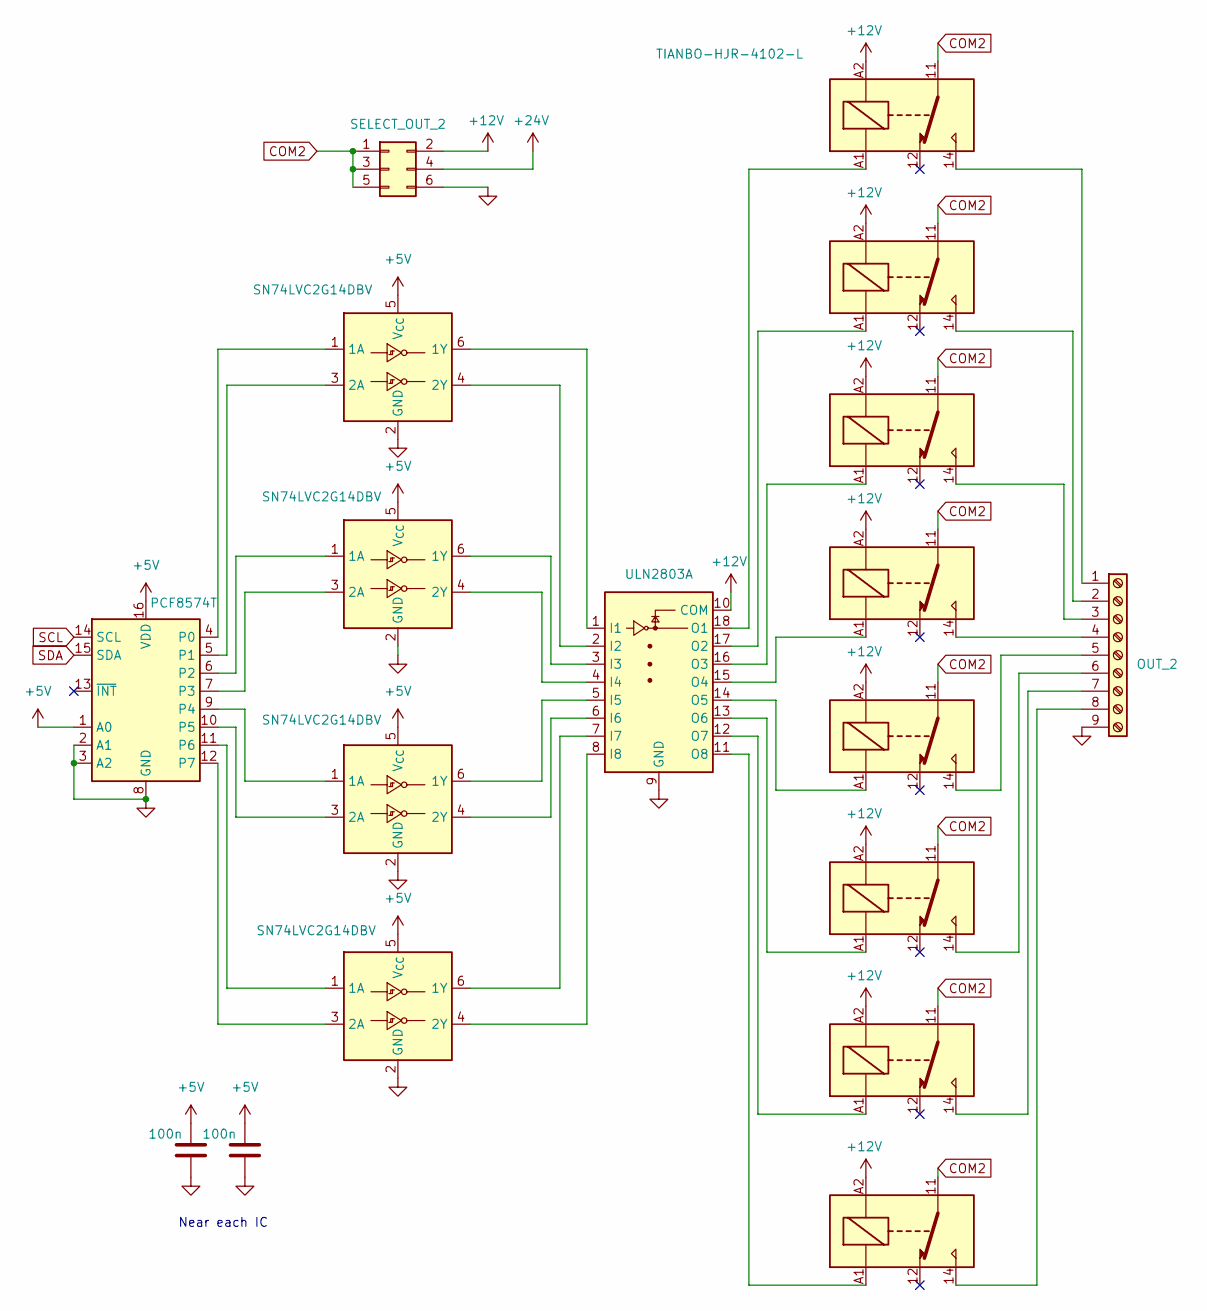
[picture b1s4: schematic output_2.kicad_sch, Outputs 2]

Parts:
C31, C32: 100n; C_1206_3216Metric
J6: SELECT_OUT_2; PinHeader_2x03_P2.54mm_Vertical
J12: OUT_2; TerminalBlock_MaiXu_MX126-5.0-09P_1x09_P5.00mm
K3, K4, K5, K6, K7, K8, K9, K10: TIANBO-HJR-4102-L; Relay_SPDT_CUI_SR5
U9: PCF8574T; SOIC-16W_7.5x10.3mm_P1.27mm
U10, U11, U12, U13: SN74LVC2G14DBV; SOT-23-6
U14: ULN2803A; SOIC-18W_7.5x11.6mm_P1.27mm

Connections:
+5V: C31.1, C32.1, U9.1 (A0), U9.16 (VDD), U10.5 (V_{CC}), U11.5 (V_{CC}), U12.5 (V_{CC}), U13.5 (V_{CC}); also elsewhere on the board
+12V: J6.2, K3.A2, K4.A2, K5.A2, K6.A2, K7.A2, K8.A2, K9.A2, K10.A2, U14.10 (COM); also elsewhere on the board
+24V: J6.4; also elsewhere on the board
COM2: J6.1, J6.3, J6.5, K3.11, K4.11, K5.11, K6.11, K7.11, K8.11, K9.11, K10.11
GND: C31.2, C32.2, J6.6, J12.9, U9.2 (A1), U9.3 (A2), U9.8 (GND), U10.2 (GND), U11.2 (GND), U12.2 (GND), U13.2 (GND), U14.9 (GND); also elsewhere on the board
unnamed: J12.1, K10.14
unnamed: J12.2, K3.14
unnamed: J12.3, K4.14
unnamed: J12.4, K5.14
unnamed: J12.5, K6.14
unnamed: J12.6, K7.14
unnamed: J12.7, K8.14
unnamed: J12.8, K9.14
unnamed: U9.4 (P0), U10.1 (1A)
unnamed: U10.6 (1Y), U14.1 (I1)
unnamed: U9.5 (P1), U10.3 (2A)
unnamed: U10.4 (2Y), U14.2 (I2)
unnamed: U9.6 (P2), U11.1 (1A)
unnamed: U11.6 (1Y), U14.3 (I3)
unnamed: U9.7 (P3), U11.3 (2A)
unnamed: U11.4 (2Y), U14.4 (I4)
unnamed: U9.9 (P4), U12.1 (1A)
unnamed: U12.6 (1Y), U14.5 (I5)
unnamed: U9.10 (P5), U12.3 (2A)
unnamed: U12.4 (2Y), U14.6 (I6)
unnamed: U9.11 (P6), U13.1 (1A)
unnamed: U13.6 (1Y), U14.7 (I7)
unnamed: U9.12 (P7), U13.3 (2A)
unnamed: U13.4 (2Y), U14.8 (I8)
unnamed: K10.A1, U14.18 (O1)
unnamed: K3.A1, U14.17 (O2)
unnamed: K4.A1, U14.16 (O3)
unnamed: K5.A1, U14.15 (O4)
unnamed: K6.A1, U14.14 (O5)
unnamed: K7.A1, U14.13 (O6)
unnamed: K8.A1, U14.12 (O7)
unnamed: K9.A1, U14.11 (O8)
SCL: U9.14 (SCL); also elsewhere on the board
SDA: U9.15 (SDA); also elsewhere on the board

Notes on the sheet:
Near each IC

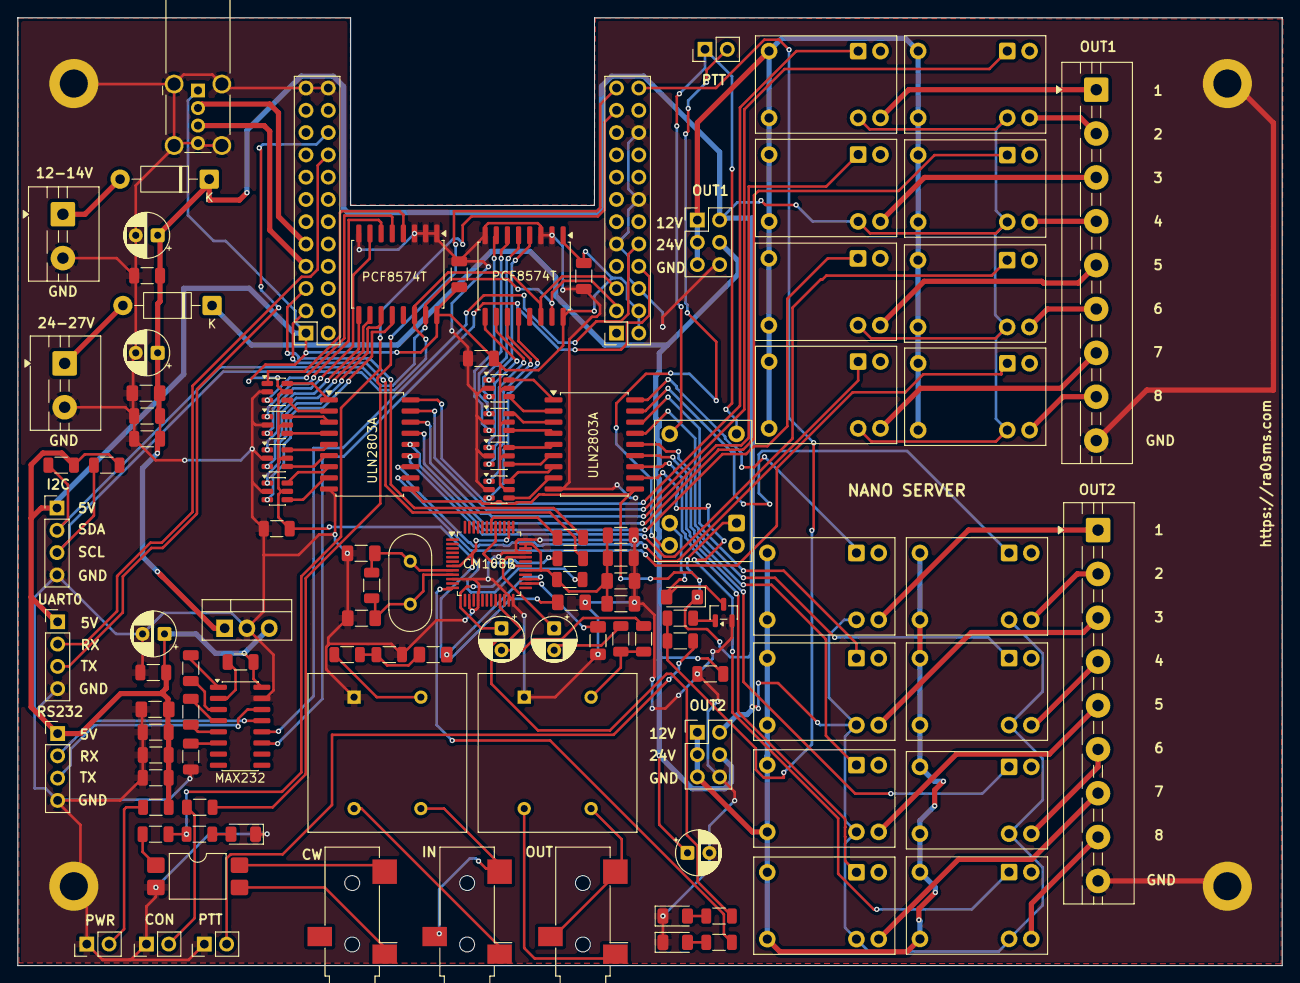
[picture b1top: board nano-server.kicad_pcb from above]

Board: 2 copper layers, 144.1 x 108.1 mm, 117 parts (0 on the bottom side), 127 nets.

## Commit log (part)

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2026-06-08 fix install script
2026-06-08 fix audio issues
2026-06-08 fix web config page
2026-06-08 add boor env setup
2026-06-08 add readme
2026-06-08 fix web relay
2026-06-08 fix i2c permition
2026-06-09 add hardware
2026-06-09 add cat control to web
2026-06-10 fix web interface issuies
2026-06-11 add KiCad files and fix readme
2026-06-11 fix readme
2026-06-18 add kenwood protocol realisation
2026-06-18 change the web interface for all settings
2026-06-18 fix audio web interface issues
2026-06-18 del web_config srvice (all moved to app.py)
2026-06-19 fix audio control tab
2026-06-19 fix audio number of channel issue
2026-06-19 fix audio capture issue
2026-06-19 add band decoder for relay
2026-06-19 fix band plan boards
2026-06-20 add auto update for Main tab
2026-06-21 change some pics and update ReadMe
2026-06-21 add winkeyer support
2026-06-21 fix morse code issuies
2026-06-22 add some pictures
2026-06-25 add new trx tab
2026-06-25 fix mode selection issue
2026-06-25 remove some functions on trx tab
2026-06-25 fix trx tab finally
2026-06-25 fix trx tab
2026-06-25 del some debug print()
2026-06-29 improve ptt service
